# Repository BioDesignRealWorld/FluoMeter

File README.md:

FluoMeter
=========

This repository contains all technical files (CAD drawings, PCB files,
firmware) to reproduce a quantitative fluorescence measurement device. This
device was created by the [BioDesign for the Real-World](http://biodesign.cc)
project to be used together with a bio-reporter for arsenic or other heavy
metal detection.

* [Chronology and principle of the device](http://wiki.biodesign.cc/wiki/Chronology_of_the_prototypes)
* [Build the FluoMeter](http://wiki.biodesign.cc/wiki/Arsenic-Prototype-4-0)
* [BioDesign wiki](http://wiki.biodesign.cc)
* [BioDesign blog](http://biodesign.cc)
* [Arsenic biosensors literature](http://www.unil.ch/arsenicsensors/en/home/menuguid/literature.html)

What is the BioDesign for the Real-World project ?
--------------------------------------------------

BIO-DESIGN for the REAL WORLD is a transdisciplinary and collaborative research
project to define, build, and field-test prototypes that require the
integration of wetware, hardware, and software to visualise and address real
world water problems.

The project is a partnership between (Art)ScienceBLR with design students from
the Srishti School of Art, Design & Technology, (Bangalore, India) the
Lifepatch citizen initiative in art, science and technology (Yogyakarta,
Indonesia), and students at the School of Life Sciences at EPFL (Lausanne,
Switzerland, and housed in Hackuarium). We collaborate closely with
National Centre for Biological Sciences (NCBS, Bangalore India),
and Universitas Gadjah Mada (Yogyakarta, Indonesia).

We follow the open process – CC BY-SA 3.0 and a do-it-yourself (DIY) and do-it-with-others DIWO) approach. Our documentation can be found on the project wiki and we share our code and designs on github. Be sure to check out our videos and links.

BioDesign started as an idea in the hackterialab 2011 in Romainmôtier in Switzerland. We are part of the hackteria network. Check out Hackteria’s wiki page for other DIYBIO projects and designs.

The project was launched with support by the CoDEV SEED grant from EPFL (2.2013-12.2014).

Contributors
------------

* Sachiko Hirosue
* Robin Scheibler
* Emilie Mussard
* Romain Equey
* Jasmina Rubattel
* Nicolas Krischer
* Bastien Orset
* Falco Enzler
* Thomas Vetterli
* Dounia Droubi
* Marie Duc
* Colombine Verzat
* Marie Willemin
* Mathilde Vidal

Collaborators at large
----------------------

* [Lifepatch](http://lifepatch.org/)
* [(Art)ScienceBLR](http://artscienceblr.org/)
* [Lab of environmental and evolutionary microbiology (UNIL)](http://www.unil.ch/dmf/en/home/menuinst/research-units/van-der-meer.html)
* [Microsystems laboratory 4 (EPFL)](http://lmis4.epfl.ch/)

License
-------

(c) 2015 Biodesign for the Real-World

This is an open-source hardware project shared under the CC-BY-SA. You can
modify, remix, reuse and redistribute this work as long as it is under the same
conditions. See the terms of the license below for more details.

<br /><span xmlns:dct="http://purl.org/dc/terms/" property="dct:title">FluoMeter</span> by <a xmlns:cc="http://creativecommons.org/ns#" href="http://biodesign.cc" property="cc:attributionName" rel="cc:attributionURL">BioDesign for the Real-World</a> is licensed under a <a rel="license" href="http://creativecommons.org/licenses/by-sa/4.0/">Creative Commons Attribution-ShareAlike 4.0 International License</a>.<br />Based on a work at <a xmlns:dct="http://purl.org/dc/terms/" href="https://github.com/BioDesignRealWorld/FluoMeter" rel="dct:source">https://github.com/BioDesignRealWorld/FluoMeter</a>.

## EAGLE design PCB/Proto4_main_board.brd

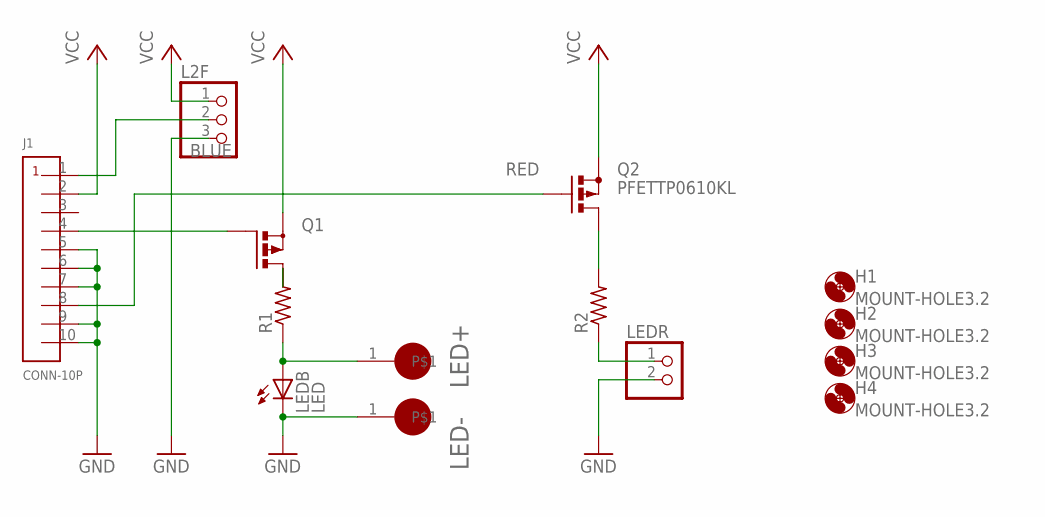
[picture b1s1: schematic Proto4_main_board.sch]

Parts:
H1, H2, H3, H4: MOUNT-HOLE3.2; 3,2
J1: CONN-10P; MICROMATCH-10P-SMD
L2F: PINHD-1X3/90; 1X03/90
LED+: TP; LARGE_PAD
LED-: TP; LARGE_PAD
LEDB: LED; CREE-XP-E2
LEDR: PINHD-1X2/90; 1X02/90
Q1: PMOSFET_PTO220BH; TO220BH
Q2: PFETTP0610KL; TO92-OVAL
R1: R-US_0414/15; 0414/15
R2: R-US_0309/12; 0309/12

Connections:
BLUE: J1.4, Q1.G
GND: J1.5, J1.6, J1.7, J1.9, J1.10, L2F.3, LED-.1, LEDB.2 (C), LEDR.2
unnamed: Q1.D, R1.2
unnamed: LED+.1, LEDB.1 (A), R1.1
unnamed: Q2.3 (D), R2.2
unnamed: LEDR.1, R2.1
unnamed: J1.1, L2F.2
RED: J1.8, Q2.2 (G)
VCC: J1.2, L2F.1, Q1.S, Q2.1 (S)

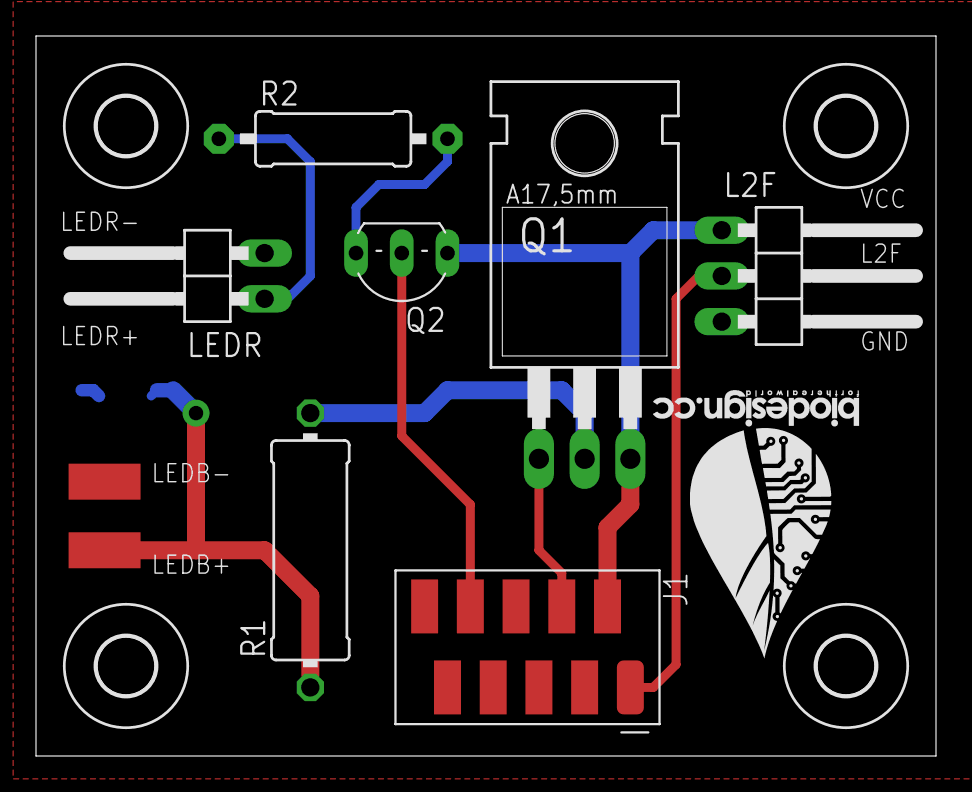
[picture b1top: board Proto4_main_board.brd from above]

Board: 2 copper layers, 50.0 x 40.0 mm, 15 parts (1 on the bottom side), 9 nets.

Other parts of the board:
U$1: BIODESIGN-LOGO

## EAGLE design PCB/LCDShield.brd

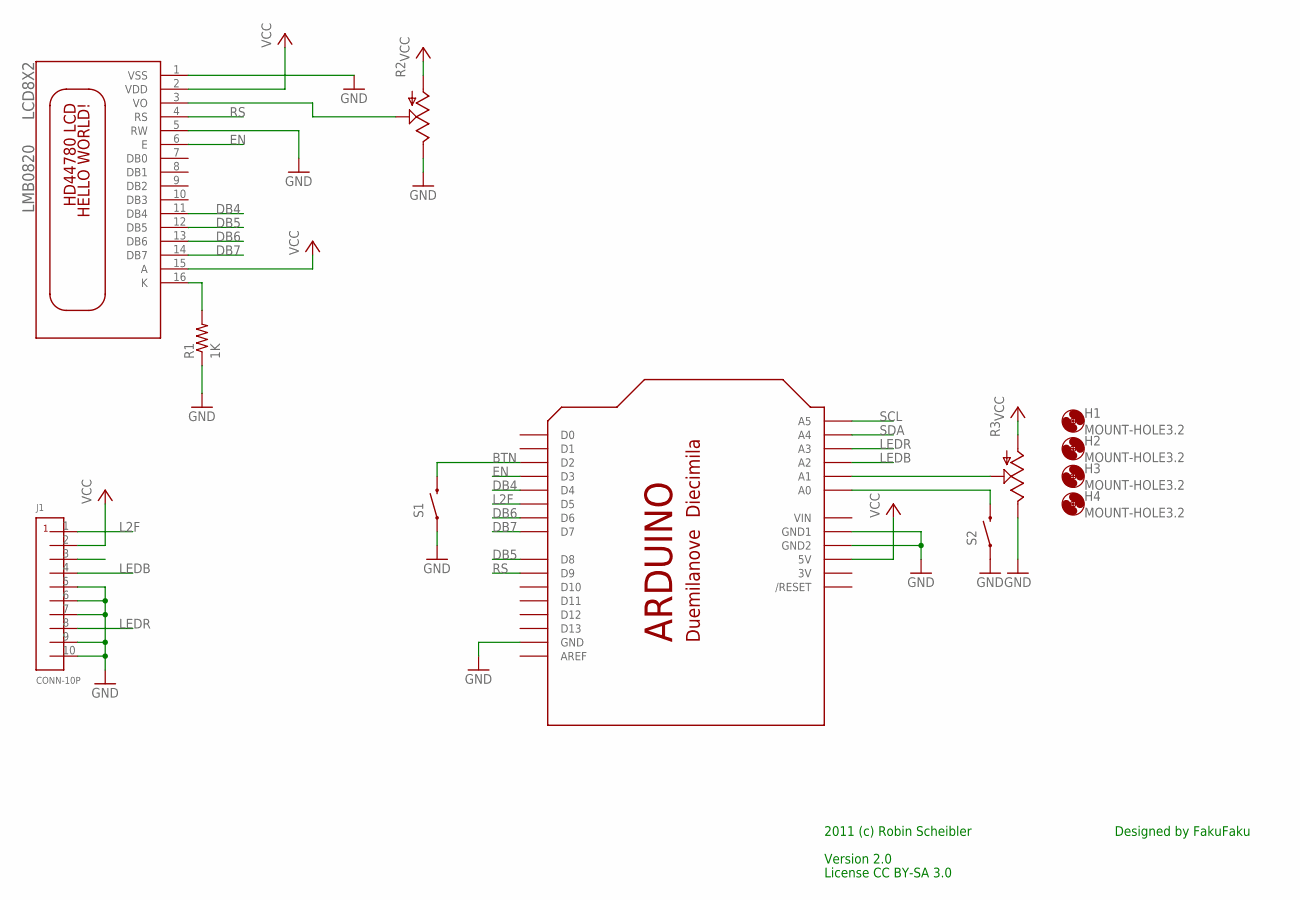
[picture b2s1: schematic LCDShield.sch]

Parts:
H1, H2, H3, H4: MOUNT-HOLE3.2; 3,2
J1: CONN-10P; MICROMATCH-10P-SMD
LCD8X2: LMB0820
R1: 1K; 0207/10
R2: POTTRIM; TRIM_POT
R3: POT; ALPS_POT
S1, S2: SWITCH-MOMENTARY-2PTH; TACTILE-PTH
SHIELD: ARDUINOSHIELD-PINS; ARDUINO-PINS

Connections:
3V: SHIELD.3V
BTN: S1.3 (2), SHIELD.D2
CON3: J1.3
DB4: LCD8X2.11 (DB4), SHIELD.D4
DB5: LCD8X2.12 (DB5), SHIELD.D8
DB6: LCD8X2.13 (DB6), SHIELD.D6
DB7: LCD8X2.14 (DB7), SHIELD.D7
EN: LCD8X2.6 (E), SHIELD.D3
GND: J1.5, J1.6, J1.7, J1.9, J1.10, LCD8X2.1 (VSS), LCD8X2.5 (RW), R1.1, R2.2 (E), R3.P$1 (E), S1.1, S2.1, SHIELD.GND, SHIELD.GND1, SHIELD.GND2
L2F: J1.1, SHIELD.D5
LEDB: J1.4, SHIELD.A2
LEDR: J1.8, SHIELD.A3
unnamed: LCD8X2.16 (K), R1.2
unnamed: LCD8X2.3 (VO), R2.1 (S)
unnamed: S2.3 (2), SHIELD.A0
unnamed: R3.P$2 (S), SHIELD.A1
RS: LCD8X2.4 (RS), SHIELD.D9
SCL: SHIELD.A5
SDA: SHIELD.A4
VCC: J1.2, LCD8X2.2 (VDD), LCD8X2.15 (A), R2.3 (A), R3.P$3 (A), SHIELD.5V
VIN: SHIELD.VIN

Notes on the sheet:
Version 2.0
License CC BY-SA 3.0
Designed by FakuFaku
2011 (c) Robin Scheibler

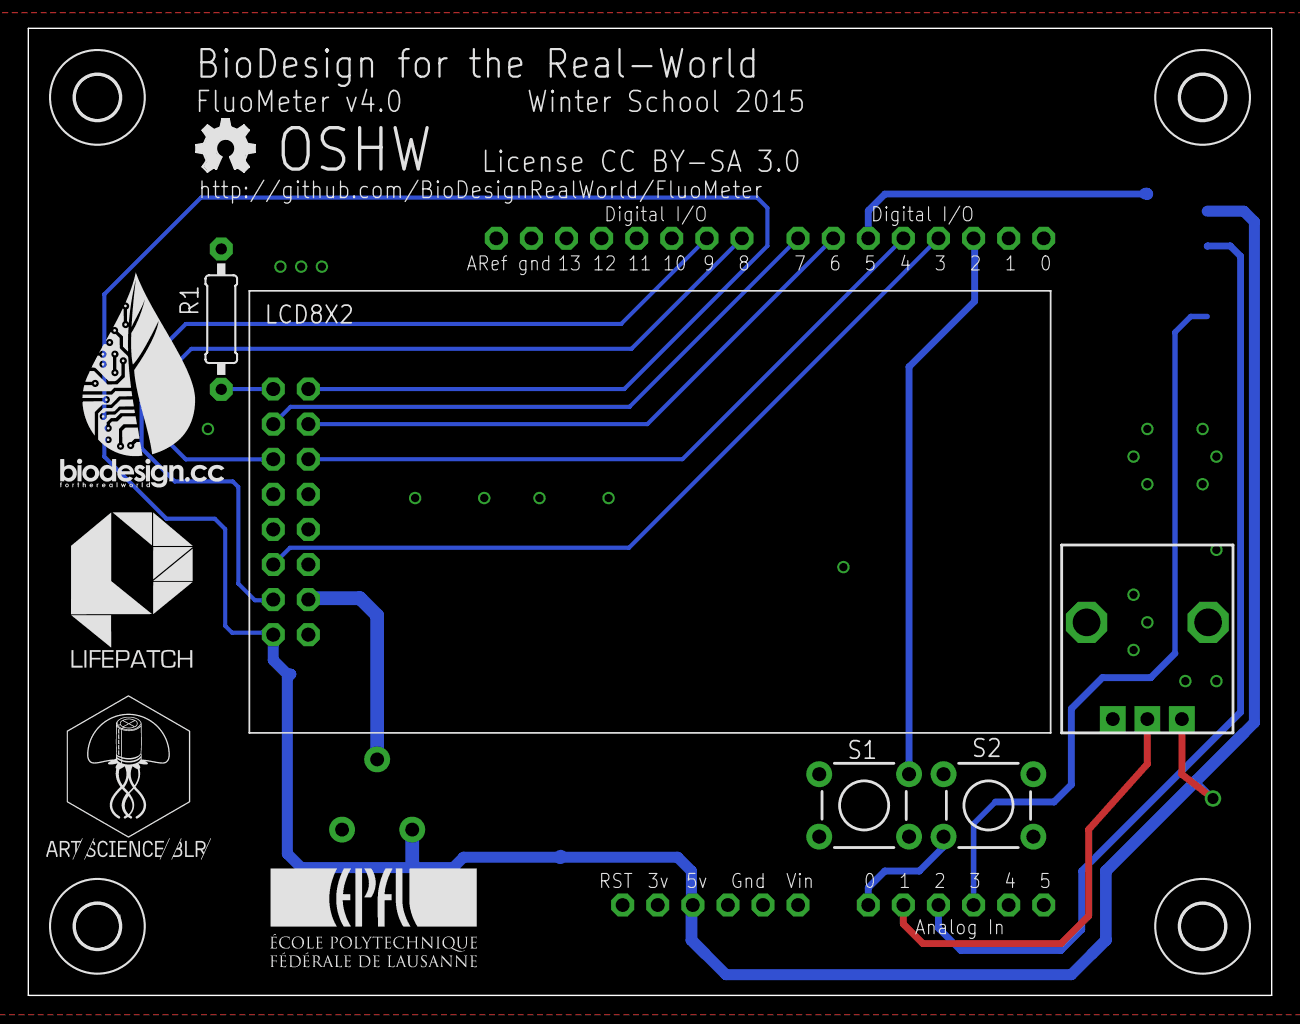
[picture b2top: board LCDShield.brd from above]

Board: 2 copper layers, 90.0 x 70.0 mm, 17 parts (1 on the bottom side), 16 nets.

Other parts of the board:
U$1: BIODESIGN
U$4: OSHW_FILLX150_NOTEXT
U$5: LIFEPATCH
U$6: ARTSCIENCEBLR
U$7: EPFL_LOGO_15MM

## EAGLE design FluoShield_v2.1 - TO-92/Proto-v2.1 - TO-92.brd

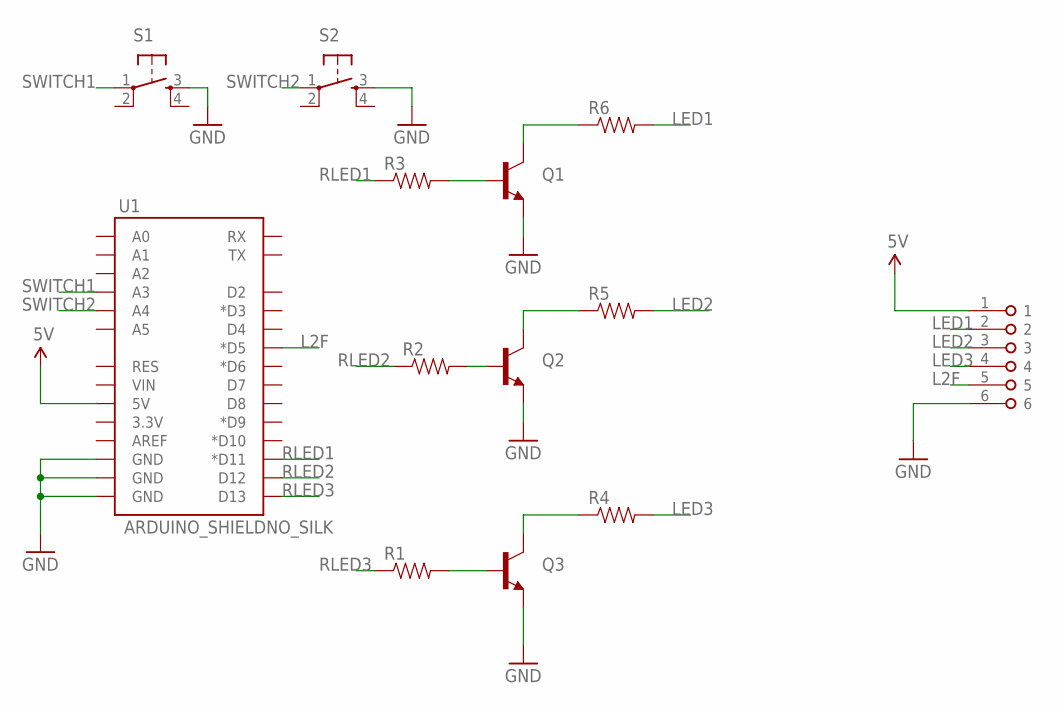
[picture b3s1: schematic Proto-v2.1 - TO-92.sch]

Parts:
Q1, Q2, Q3: TRANSISTOR_NPNBC547; TO-92-AMMO
R1, R2, R3, R4, R5, R6: RESISTORAXIAL-0.3; AXIAL-0.3
S1, S2: TAC_SWITCHPTH; TACTILE-PTH
U1: ARDUINO_SHIELDNO_SILK; DUEMILANOVE_VIAS
U$1: TERMINAL-6; MBE-156

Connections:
5V: U1.5V, U$1.1
GND: Q1.3 (E), Q2.3 (E), Q3.3 (E), S1.3, S2.3, U1.GND@0 (GND), U1.GND@1 (GND), U1.GND@2 (GND), U$1.6
L2F: U1.D5 (*D5), U$1.5
LED1: R6.P$2 (2), U$1.2
LED2: R5.P$2 (2), U$1.3
LED3: R4.P$2 (2), U$1.4
unnamed: Q3.2 (B), R1.P$2 (2)
unnamed: Q2.2 (B), R2.P$2 (2)
unnamed: Q3.1 (C), R4.P$1 (1)
unnamed: Q2.1 (C), R5.P$1 (1)
unnamed: Q1.2 (B), R3.P$2 (2)
unnamed: Q1.1 (C), R6.P$1 (1)
RLED1: R3.P$1 (1), U1.D11 (*D11)
RLED2: R2.P$1 (1), U1.D12
RLED3: R1.P$1 (1), U1.D13
SWITCH1: S1.1, U1.A3
SWITCH2: S2.1, U1.A4

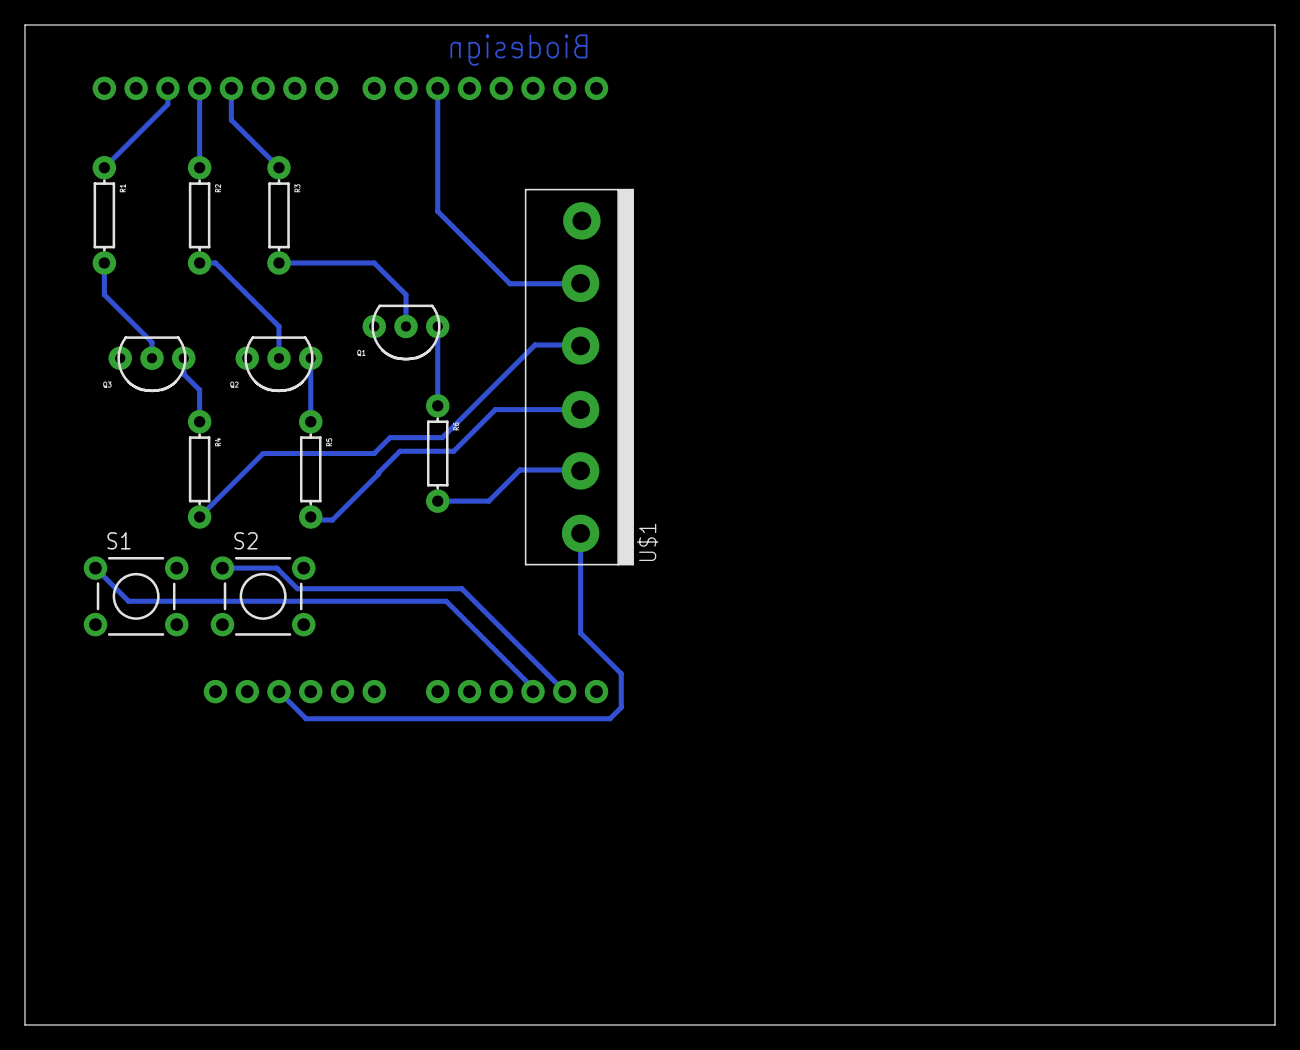
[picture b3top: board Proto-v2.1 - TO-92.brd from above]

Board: 2 copper layers, 100.0 x 80.0 mm, 13 parts (0 on the bottom side), 17 nets.

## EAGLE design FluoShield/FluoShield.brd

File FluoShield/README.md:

FluoShield
==========

An Arduino shield for the fluorescence meter of BioDesign for the Real-World.

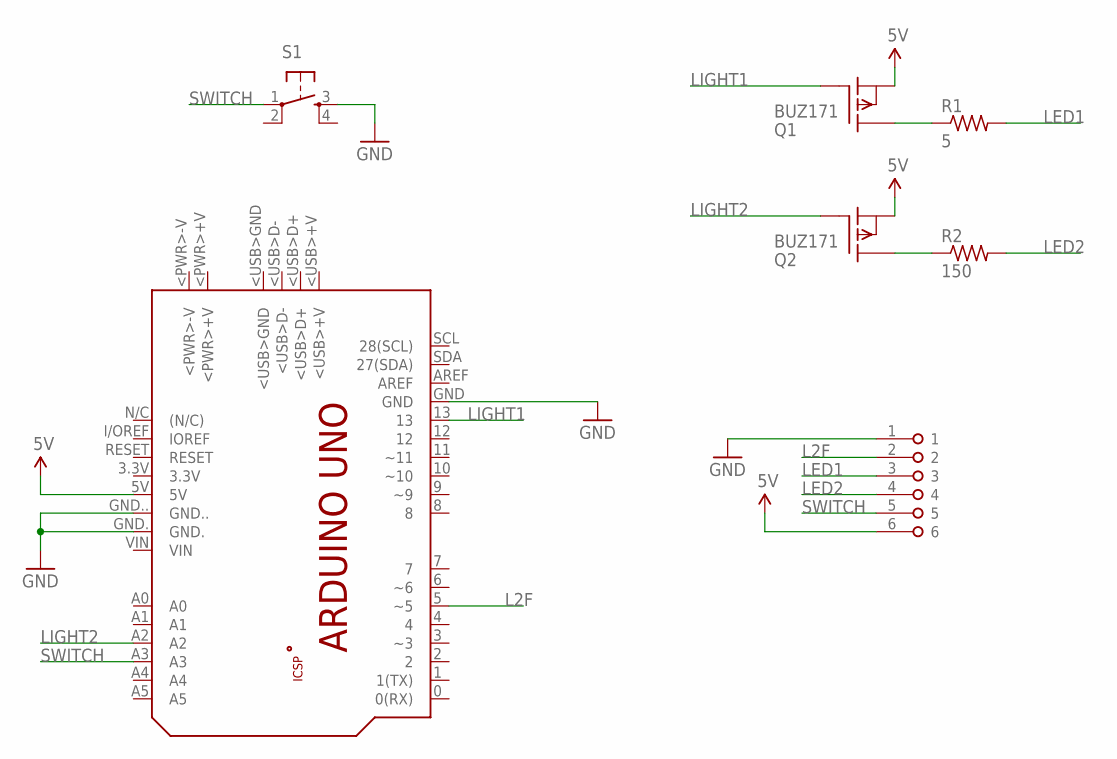
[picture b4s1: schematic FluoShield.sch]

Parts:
PCB1: ARDUINO_UNO
Q1, Q2: BUZ171; TO220
R1: 5; 0207/10
R2: 150; 0207/10
S1: TAC_SWITCHPTH; TACTILE-PTH
U$4: TERMINAL-6; MBE-156

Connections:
5V: PCB1.5V, Q1.3 (S), Q2.3 (S), U$4.6
GND: PCB1.GND, PCB1.GND., PCB1.GND.., S1.3, U$4.1
L2F: PCB1.5 (~5), U$4.2
LED1: R1.2, U$4.3
LED2: R2.2, U$4.4
LIGHT1: PCB1.13, Q1.1 (G)
LIGHT2: PCB1.A2, Q2.1 (G)
unnamed: Q1.2 (D), R1.1
unnamed: Q2.2 (D), R2.1
SWITCH: PCB1.A3, S1.1, U$4.5

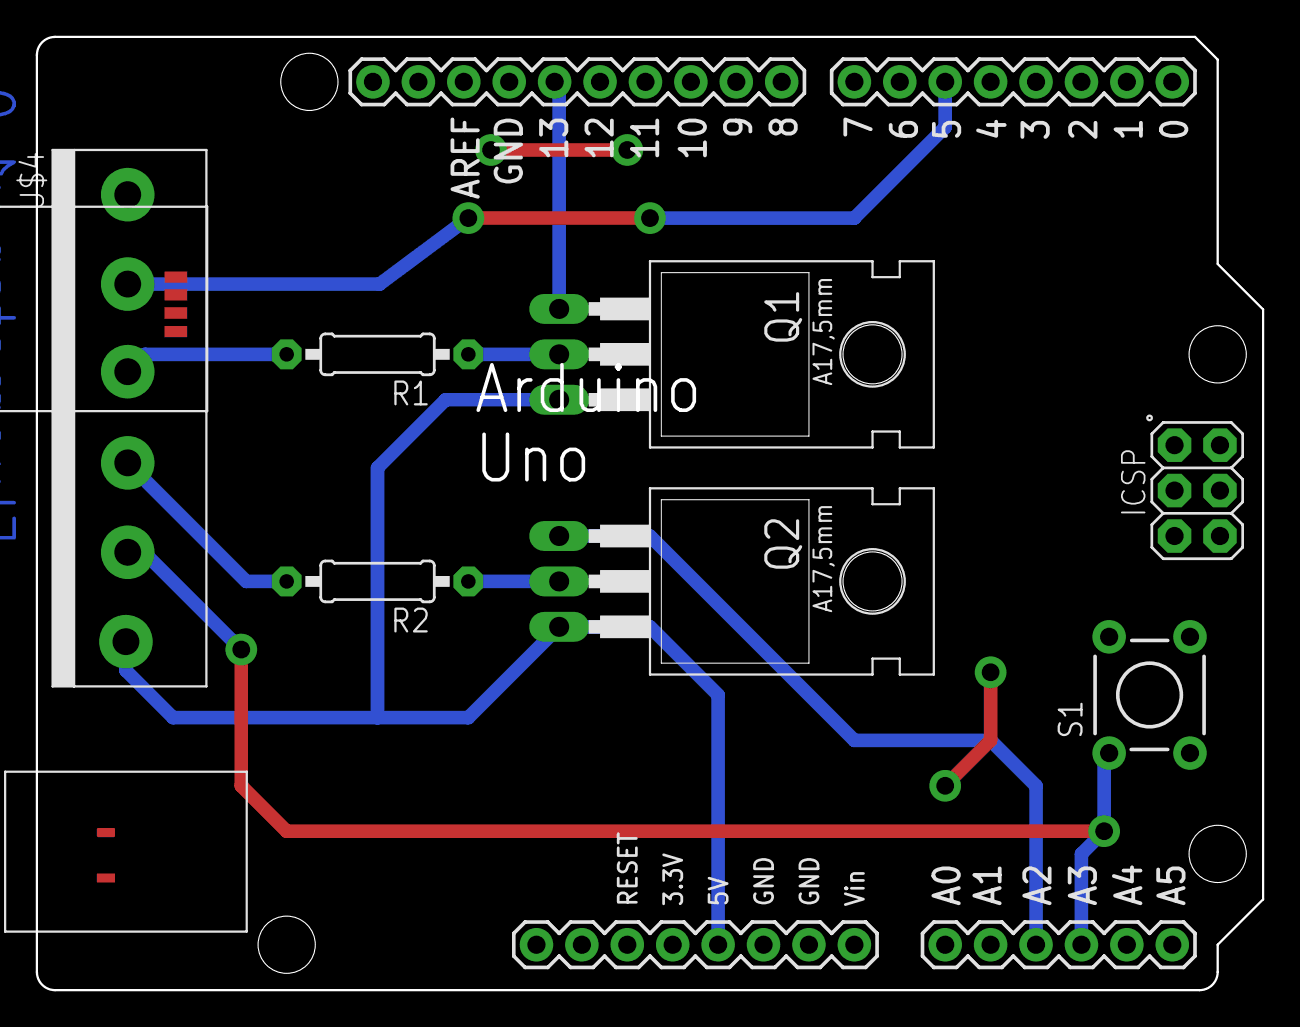
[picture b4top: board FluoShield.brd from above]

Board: 2 copper layers, 68.6 x 53.3 mm, 7 parts (0 on the bottom side), 10 nets.

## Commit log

2014-03-25 changed integration time
2014-03-25 changed serial speed.
2014-05-29 FluoAndTurbMeter
2014-05-29 Rename FluoAndTurbMeter to FluoAndTurbMeter.ino
2014-09-16 Eagle files for the Fluorescence detector Arduino shield.
2014-09-16 Renamed the sketch to old name.
2015-03-11 Added the v2.1 PCB design
2015-07-17 Now displaying both numbers together on the script. Also count is 60000 ms.
2015-08-11 back to count 30000ms
2016-01-06 Switched to prototype v4.0 for the winter school.
2016-01-06 Improved README.
2016-02-04 Paper Box Lasercut Template
    Winter School 4.0
2016-02-05 Fixed bug that caused the overflow interrupt of the counter to be executed one start, leading to higher count for the first count after start.
2016-02-05 Fixed bug that caused the button interrupt to be executed immediately after power on.
2016-05-27 Added Arduino mega support for the hardware counter through Timer5 (digital pin 47).

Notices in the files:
parts and their libraries:
SparkFun-DiscreteSemi: Licensing: Creative Commons ShareAlike 4.0 International - https://creativecommons.org/licenses/by-sa/4.0
